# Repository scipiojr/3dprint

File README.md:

# 3dprint

Konstruktionen für den 3D-Druck, je Projekt ein Unterordner.

| Ordner | Inhalt |
|---|---|
| [`pooldach-bestway-56448`](pooldach-bestway-56448/) | Satteldach für den Ovalpool Bestway Power Steel 56448: Hub, Randhalter (OpenSCAD), Rechner |

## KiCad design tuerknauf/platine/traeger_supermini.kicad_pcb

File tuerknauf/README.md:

# Türknauf für einen steckenden Schlüssel (Winkhaus-Profilzylinder)

Drehknauf für die Innenseite einer Haustür, in deren Profilzylinder dauerhaft ein Schlüssel steckt. Der Knauf ersetzt die Rosette und schützt den Schlüssel vor dem Verbiegen: Der Griff läuft auf einem Lagerbund der Platte, sodass Querkräfte über Platte und Türschrauben in die Tür gehen und der Schlüssel nur noch gedreht wird. Ein bündig eingelegtes Haus auf dem Griff zeigt die Stellung des Schlüssels (Dach oben = Schlüssel hochkant).

| Platte | Griff |
|---|---|
|  |  |

## Dateien

| Datei | Inhalt |
|---|---|
| `schluesselknauf.scad` | Parametrische Vorlage für alle Teile (OpenSCAD 2021.01). Teil über `teil` wählen. |
| `bilder/` | Vorschaubilder. |

Die STL-Dateien werden nicht eingecheckt; sie entstehen aus der SCAD-Datei (`teil` setzen, F6, als STL exportieren).

## Teile

| `teil` | Anzahl | Beschreibung |
|---|---|---|
| `platte` | 1 | Beschlag mit Lagerbund (Ø 32, 14 mm hoch), wird mit den vorhandenen Türschrauben befestigt |
| `schaft` | 1 | Gabel, die den Schlüsselkopf umfasst; der Flansch läuft hinter dem Deckel der Platte |
| `griff` | 1 | Knauf Ø 56 mit Griffmulden, läuft auf dem Lagerbund |
| `haus` | 1 | Einsatz für die Stellungsanzeige, bündig im Griff (zweite Farbe) |
| `kappe_kopf`, `kappe_mutter` | je 1 | Gewindekappen M8 × 1 für die beiden Öffnungen der Querschraube im Griff |
| `kappe` | 2 | Abdeckungen für die Türschrauben in der Platte |

Kaufteile: 1 Zylinderschraube M3 × 30 (Rundkopf) mit M3-Mutter. M4 passt nicht durch das 3,7-mm-Loch im Schlüssel.

## Anpassen

Die Maße des eigenen Schlüssels und der Tür stehen im Abschnitt „gemessen“ am Anfang der SCAD-Datei:

- `c` – Stirnfläche des Zylinders über der Türoberfläche
- `k_breite`, `k_dicke`, `k_laenge`, `k_hals` – Schlüsselkopf und Hals
- `pin_z` – Mitte des Schlüssellochs über der Schulter
- `schraub_abst` – Abstand der Türschrauben
- `gr_d` – Griffdurchmesser (56 mm, damit der Daumen nicht mehr zwischen Griff und Türdrücker gerät)

Die Prüfungen (`assert`) melden, wenn Bund, Querschraube oder Wände nicht mehr zusammenpassen.

## Druck

- PETG (ABS oder TPU 68D gehen auch), 4–5 Wandlinien (Orca Slicer: „Wandschleifen“), 40 % Füllung, 0,2 mm Schichthöhe.
- Platte mit der Rückseite (Türseite) auf das Druckbett, ohne Stützen.
- Griff, Haus und Gewindekappen mit der Oberseite nach unten drucken (aus OpenSCAD kommen sie in Einbaulage, also im Slicer um 180° um X drehen).
- Haus zusammen mit dem Griff als ein Objekt laden und dem Haus ein eigenes Filament zuweisen.

## Montage

1. Alte Rosette abschrauben, der Schlüssel bleibt stecken.
2. Schaft über den Schlüssel schieben: Der Hals läuft durch den Schlitz im Flansch, der Kopf sitzt in der Gabel.
3. Platte darüber setzen, sodass der Flansch des Schafts in der Kammer hinter dem Deckel liegt, und mit den vorhandenen Türschrauben festschrauben. Die beiden Kappen in die Schraubenlöcher stecken.
4. Griff auf den Lagerbund setzen und drehen, bis Bohrung im Griff, Gabel und Schlüsselloch fluchten. Das Haus zeigt dabei nach oben, wenn der Schlüssel hochkant steht.
5. M3 × 30 von der Kopfseite durchstecken, Mutter auf der Gegenseite in die Sechskanttasche legen und anziehen.
6. Gewindekappen mit einem Schlitzschraubendreher eindrehen (`kappe_kopf` über dem Schraubenkopf, `kappe_mutter` über der Mutter).

## Smarthome-Variante

Dieser Stand enthält zusätzlich den Verschlusssensor: Mit `elektronik = true` (Voreinstellung) entstehen die verlängerte Platte mit Elektronikfach, Lichtfenster und Reset-Loch sowie der Griff mit Magnettaschen. Platinen, Firmware, Bestellung und Einbau beschreibt [SMARTHOME.md](SMARTHOME.md). Mit `elektronik = false` entsteht der reine Knauf.

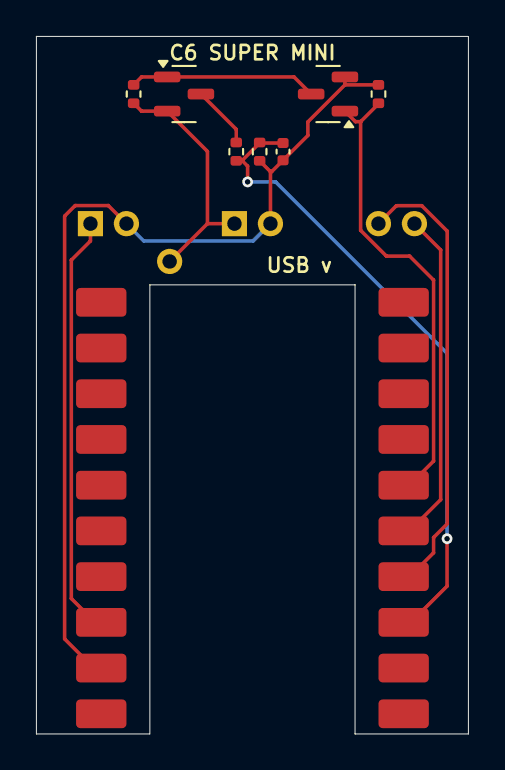
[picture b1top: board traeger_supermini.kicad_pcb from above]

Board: 2 copper layers, 24.0 x 38.8 mm, 9 parts (0 on the bottom side), 9 nets.

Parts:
C3: 100nF; C_0402_1005Metric
J1: Kabel; Loetaugen_7x_D0.8mm
Q1: 2N7002; SOT-23
Q2: AO3401A; SOT-23
R1, R2: 100k; R_0402_1005Metric
R3, R4: 1M; R_0402_1005Metric
U1: ESP32-C6_SuperMini; ESP32C6_SuperMini_Traeger

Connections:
ADC: C3.2, R1.1, R2.2, U1.3
DIV: Q2.3, R1.2
GND: C3.1, J1.2, J1.4, Q1.2, R2.1, R4.2, U1.12
MESS: Q1.1, R4.1, U1.6
PG: Q1.3, Q2.1, R3.2
SA: J1.5, U1.4
SB: J1.6, U1.5
V3V3: J1.1, U1.13
VBAT: J1.3, J1.7, Q2.2, R3.1

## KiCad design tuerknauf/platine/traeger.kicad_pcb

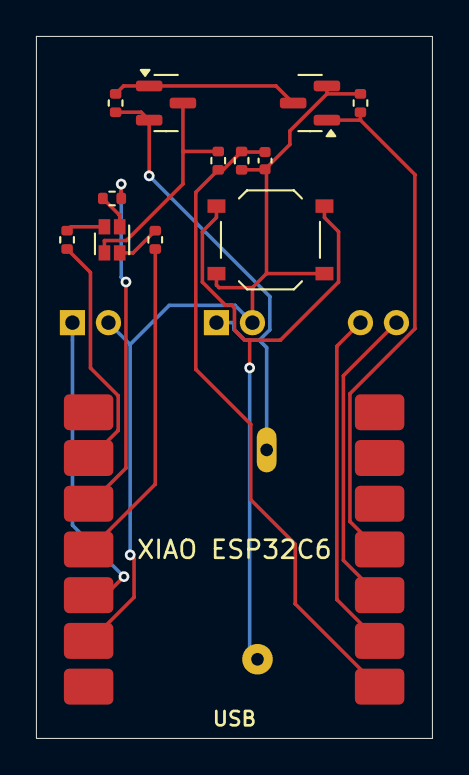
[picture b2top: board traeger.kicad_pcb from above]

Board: 2 copper layers, 22.0 x 39.0 mm, 14 parts (0 on the bottom side), 16 nets.

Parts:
C3: 100nF; C_0402_1005Metric
J1: Kabel; Loetaugen_6x_D0.8mm
LED1: LTST-C19HE1WT; LED_LiteOn_LTST-C19HE1WT
Q1: 2N7002; SOT-23
Q2: AO3401A; SOT-23
R1, R2: 100k; R_0402_1005Metric
R3, R4: 1M; R_0402_1005Metric
R5: 330; R_0402_1005Metric
R6, R7: 100; R_0402_1005Metric
SW1: TS-1187A-B-A-B; SW_Push_1P1T_XKB_TS-1187A
U1: XIAO_ESP32C6; XIAO_ESP32C6_Traeger

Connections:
ADC: C3.2, R1.1, R2.2, U1.1
DIV: LED1.4, Q2.3, R1.2
EN: SW1.1, U1.17
GND: C3.1, J1.2, J1.4, Q1.2, R2.1, R4.2, SW1.2, U1.13
KB: LED1.3, R7.2
KG: LED1.2, R6.1
KR: LED1.1, R5.2
LB: R7.1, U1.11
LG: R6.2, U1.10
LR: R5.1, U1.9
MESS: Q1.1, R4.1, U1.4
PG: Q1.3, Q2.1, R3.2
SA: J1.5, U1.2
SB: J1.6, U1.3
V3V3: J1.1, U1.12
VBAT: J1.3, Q2.2, R3.1, U1.23

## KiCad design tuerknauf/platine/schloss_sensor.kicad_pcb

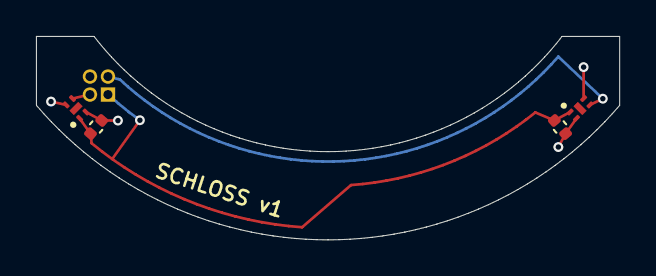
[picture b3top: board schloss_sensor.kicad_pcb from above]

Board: 2 copper layers, 32.4 x 11.3 mm, 5 parts (0 on the bottom side), 4 nets.

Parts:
C1, C2: 100nF; C_0402_1005Metric
J1: Kabel; Loetaugen_2x2_P1.0mm_D0.5mm
U1, U2: DRV5012AEDMRR; TI_X2SON-4-1EP_1.1x1.4mm_P0.5mm

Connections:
A: J1.3, U1.3
B: J1.4, U2.3
GND: C1.2, C2.2, J1.2, U1.2, U1.4, U2.2, U2.4
VCC: C1.1, C2.1, J1.1, U1.1, U2.1

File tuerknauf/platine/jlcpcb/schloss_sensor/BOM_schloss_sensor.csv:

Comment,Designator,Footprint,LCSC Part #
DRV5012AEDMRR,"U1,U2",TI_X2SON-4-1EP_1.1x1.4mm_P0.5mm,C2655038
100nF,"C1,C2",C_0402_1005Metric,C1525
